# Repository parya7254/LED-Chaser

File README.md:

# LED-Chaser
LED chaser for learning about analog sensors and killing my boredom. It will feature analog sensors and 555 timers, 10 LEDs, a potentiometer to control the speed, and a debug port!

# Why I Made This:

The reason for making this is that I really like designing PCBs for fun and also want to learn about analog sensors. I learned about 555 timers and how I could use them and also about the CD4017 IO expander. This project both gave me something to make and taught me about analog sensors.

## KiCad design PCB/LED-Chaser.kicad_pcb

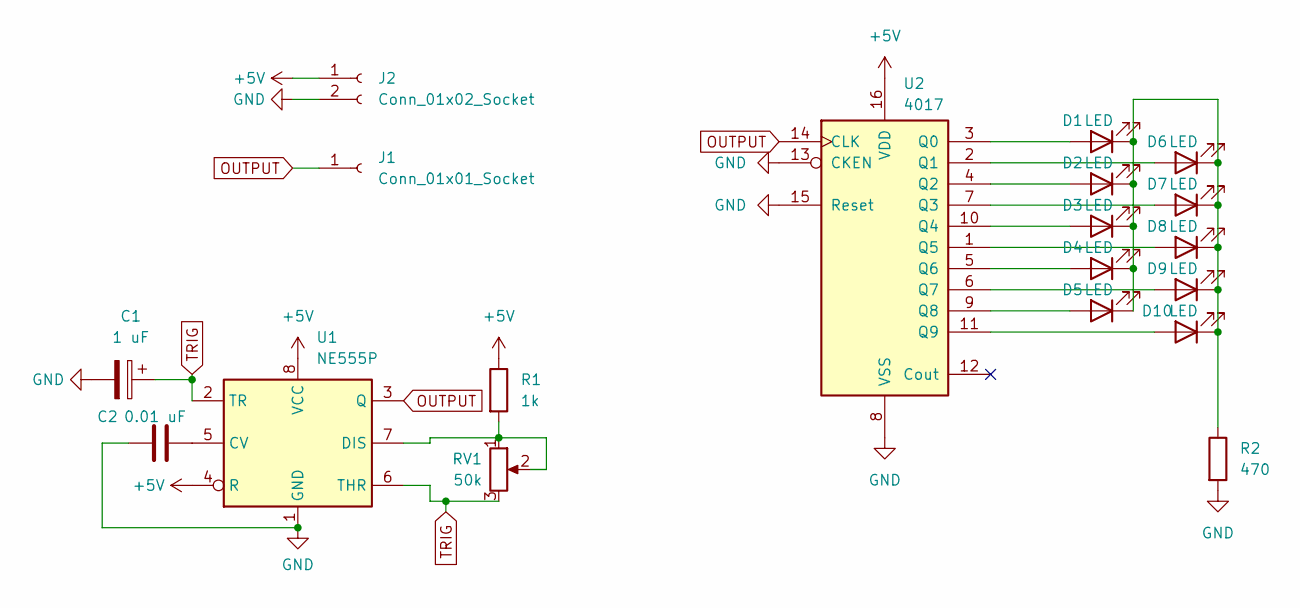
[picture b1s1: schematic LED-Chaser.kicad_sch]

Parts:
C1: 1 uF; CP_Radial_D5.0mm_P2.00mm
C2: 0.01 uF; C_Disc_D7.5mm_W2.5mm_P5.00mm
D1, D2, D3, D4, D5, D6, D7, D8, D9, D10: LED; LED_D3.0mm
J1: Conn_01x01_Socket; PinHeader_1x01_P2.54mm_Vertical
J2: Conn_01x02_Socket; PinHeader_1x02_P2.54mm_Vertical
R1: 1k; R_Axial_DIN0207_L6.3mm_D2.5mm_P7.62mm_Horizontal
R2: 470; R_Axial_DIN0207_L6.3mm_D2.5mm_P7.62mm_Horizontal
RV1: 50k; Potentiometer_Vishay_T93YA_Vertical
U1: NE555P; DIP-8_W7.62mm
U2: 4017; N16

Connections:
+5V: J2.1, R1.1, U1.4 (R), U1.8 (VCC), U2.16 (VDD)
GND: C1.2, C2.1, J2.2, R2.2, U1.1 (GND), U2.8 (VSS), U2.13 (CKEN), U2.15 (Reset)
unnamed: D1.2 (A), U2.3 (Q0)
unnamed: D1.1 (K), D2.1 (K), D3.1 (K), D4.1 (K), D5.1 (K), D6.1 (K), D7.1 (K), D8.1 (K), D9.1 (K), D10.1 (K), R2.1
unnamed: D2.2 (A), U2.4 (Q2)
unnamed: D3.2 (A), U2.10 (Q4)
unnamed: D4.2 (A), U2.5 (Q6)
unnamed: D5.2 (A), U2.9 (Q8)
unnamed: D6.2 (A), U2.2 (Q1)
unnamed: D7.2 (A), U2.7 (Q3)
unnamed: D8.2 (A), U2.1 (Q5)
unnamed: D9.2 (A), U2.6 (Q7)
unnamed: D10.2 (A), U2.11 (Q9)
unnamed: C2.2, U1.5 (CV)
unnamed: R1.2, RV1.1, RV1.2, U1.7 (DIS)
OUTPUT: J1.1, U1.3 (Q), U2.14 (CLK)
TRIG: C1.1, RV1.3, U1.2 (TR), U1.6 (THR)

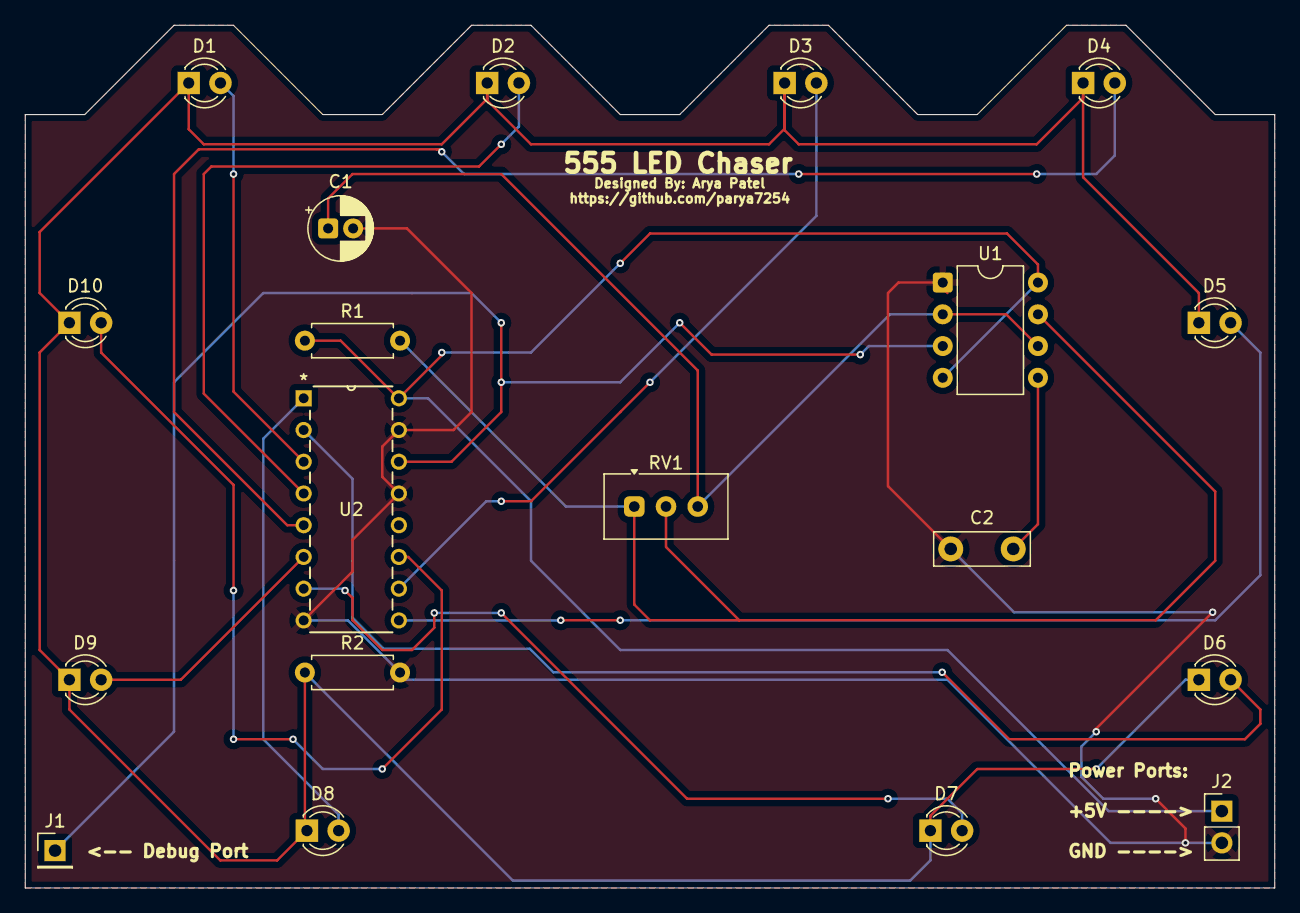
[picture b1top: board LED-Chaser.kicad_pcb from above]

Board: 2 copper layers, 100.0 x 69.1 mm, 19 parts (0 on the bottom side), 17 nets.

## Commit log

2026-05-21 Enhance README with project details and images
    Expanded project description and added images.
2026-05-21 Create placeholder
